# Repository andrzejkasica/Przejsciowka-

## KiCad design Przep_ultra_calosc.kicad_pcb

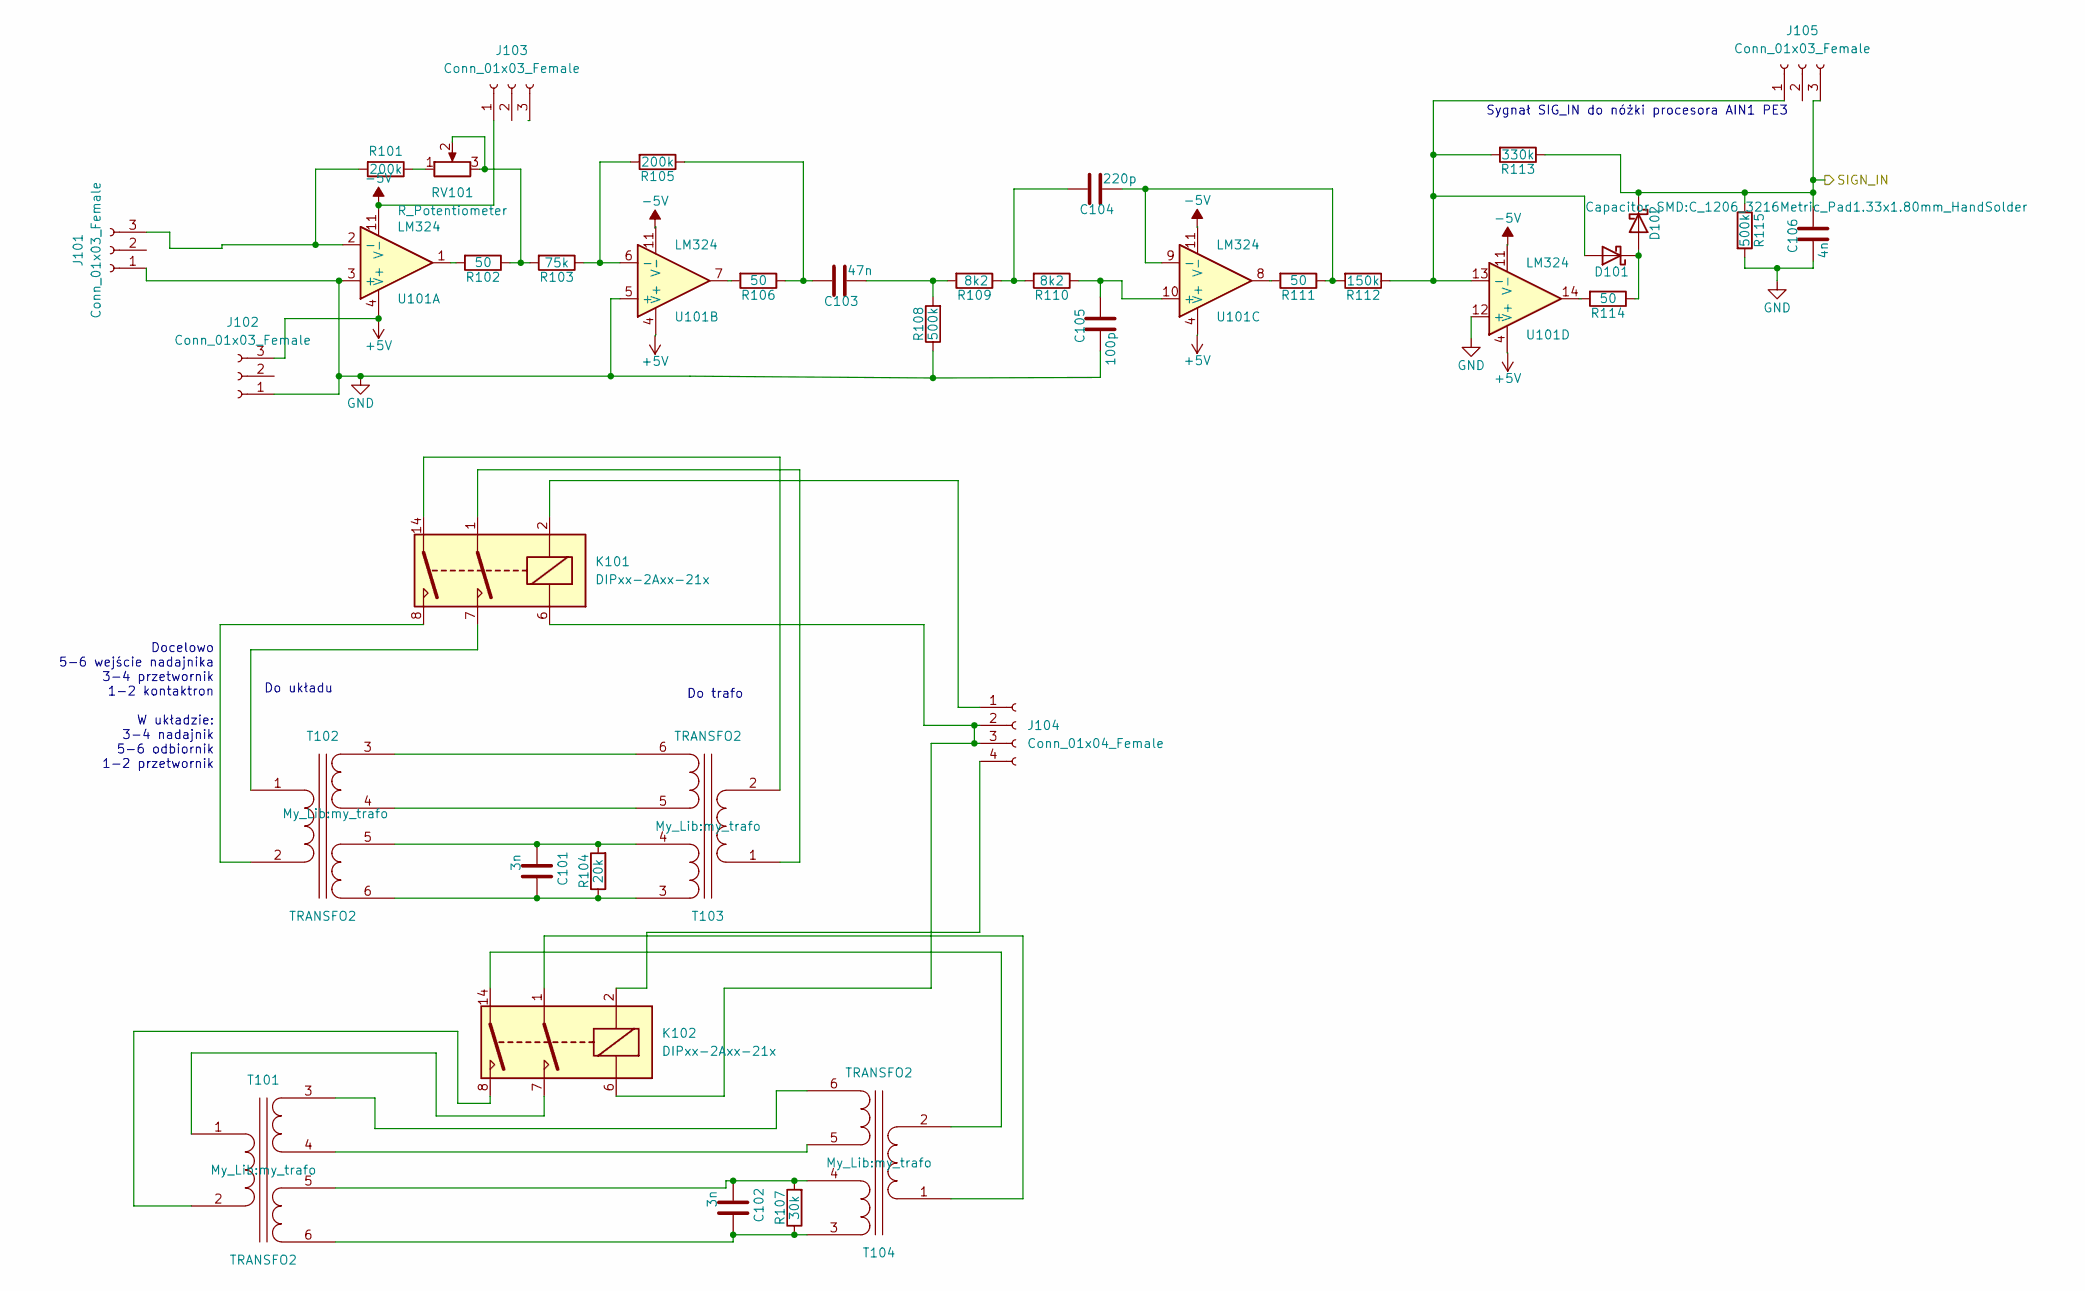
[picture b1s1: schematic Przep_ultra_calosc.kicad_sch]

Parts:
C101, C102: 3n; C_1206_3216Metric_Pad1.33x1.80mm_HandSolder
C103: 47n; C_1206_3216Metric_Pad1.33x1.80mm_HandSolder
C104: 220p; C_1206_3216Metric_Pad1.33x1.80mm_HandSolder
C105: 100p; C_1206_3216Metric_Pad1.33x1.80mm_HandSolder
C106: 4n; C_1206_3216Metric_Pad1.33x1.80mm_HandSolder
D101, D102: D_Schottky; D_MELF_Handsoldering
J101, J102, J103, J105: Conn_01x03_Female; PinHeader_1x03_P2.54mm_Vertical
J104: Conn_01x04_Female; PinHeader_1x04_P2.54mm_Vertical
K101, K102: DIPxx-2Axx-21x; Relay_StandexMeder_DIP_LowProfile
R101, R105: 200k; R_1206_3216Metric_Pad1.30x1.75mm_HandSolder
R102, R106, R111, R114: 50; R_1206_3216Metric_Pad1.30x1.75mm_HandSolder
R103: 75k; R_1206_3216Metric_Pad1.30x1.75mm_HandSolder
R104: 20k; R_1206_3216Metric_Pad1.30x1.75mm_HandSolder
R107: 30k; R_1206_3216Metric_Pad1.30x1.75mm_HandSolder
R108, R115: 500k; R_1206_3216Metric_Pad1.30x1.75mm_HandSolder
R109, R110: 8k2; R_1206_3216Metric_Pad1.30x1.75mm_HandSolder
R112: 150k; R_1206_3216Metric_Pad1.30x1.75mm_HandSolder
R113: 330k; R_1206_3216Metric_Pad1.30x1.75mm_HandSolder
RV101: R_Potentiometer; Potentiometer_Bourns_3296W_Vertical
T101, T102, T103, T104: TRANSFO2; my_trafo
U101: LM324; SOIC-14_3.9x8.7mm_P1.27mm

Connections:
+5V: J102.3, U101.4 (V+)
-5V: J103.1, U101.11 (V-)
/SIGN_IN: C106.2, D102.1 (K), J105.3, R113.1, R115.1
GND: C105.1, C106.1, J101.1, J102.1, R108.1, R115.2, U101.3 (+), U101.5 (+), U101.12 (+)
unnamed: C101.1, R104.1, T102.6 (SD), T103.3 (SA)
unnamed: C101.2, R104.2, T102.5 (SC), T103.4 (SB)
unnamed: C102.1, R107.1, T101.6 (SD), T104.3 (SA)
unnamed: C102.2, R107.2, T101.5 (SC), T104.4 (SB)
unnamed: C103.1, R108.2, R109.2
unnamed: C103.2, R105.1, R106.1
unnamed: C104.1, R111.1, R112.2, U101.9 (-)
unnamed: C104.2, R109.1, R110.2
unnamed: C105.2, R110.1, U101.10 (+)
unnamed: D101.1 (K), D102.2 (A), R114.1
unnamed: D101.2 (A), J105.1, R112.1, R113.2, U101.13 (-)
unnamed: J101.3, R101.2, U101.2 (-)
unnamed: J104.1, K101.2
unnamed: J104.2, J104.3, K101.6, K102.6
unnamed: J104.4, K102.2
unnamed: K101.1, T103.1 (AA)
unnamed: K101.7, T102.1 (AA)
unnamed: K101.8, T102.2 (AB)
unnamed: K101.14, T103.2 (AB)
unnamed: K102.1, T104.1 (AA)
unnamed: K102.7, T101.1 (AA)
unnamed: K102.8, T101.2 (AB)
unnamed: K102.14, T104.2 (AB)
unnamed: R101.1, RV101.1
unnamed: R102.1, R103.2, RV101.2, RV101.3
unnamed: R102.2, U101.1
unnamed: R103.1, R105.2, U101.6 (-)
unnamed: R106.2, U101.7
unnamed: R111.2, U101.8
unnamed: R114.2, U101.14
unnamed: T101.3 (SA), T104.6 (SD)
unnamed: T101.4 (SB), T104.5 (SC)
unnamed: T102.3 (SA), T103.6 (SD)
unnamed: T102.4 (SB), T103.5 (SC)

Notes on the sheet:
Do trafo
Docelowo 5-6 wejście nadajnika 3-4 przetwornik 1-2 kontaktron W układzie: 3-4 nadajnik 5-6 odbiornik 1-2 przetwornik
Do układu
Sygnał SIG_IN do nóżki procesora AIN1 PE3

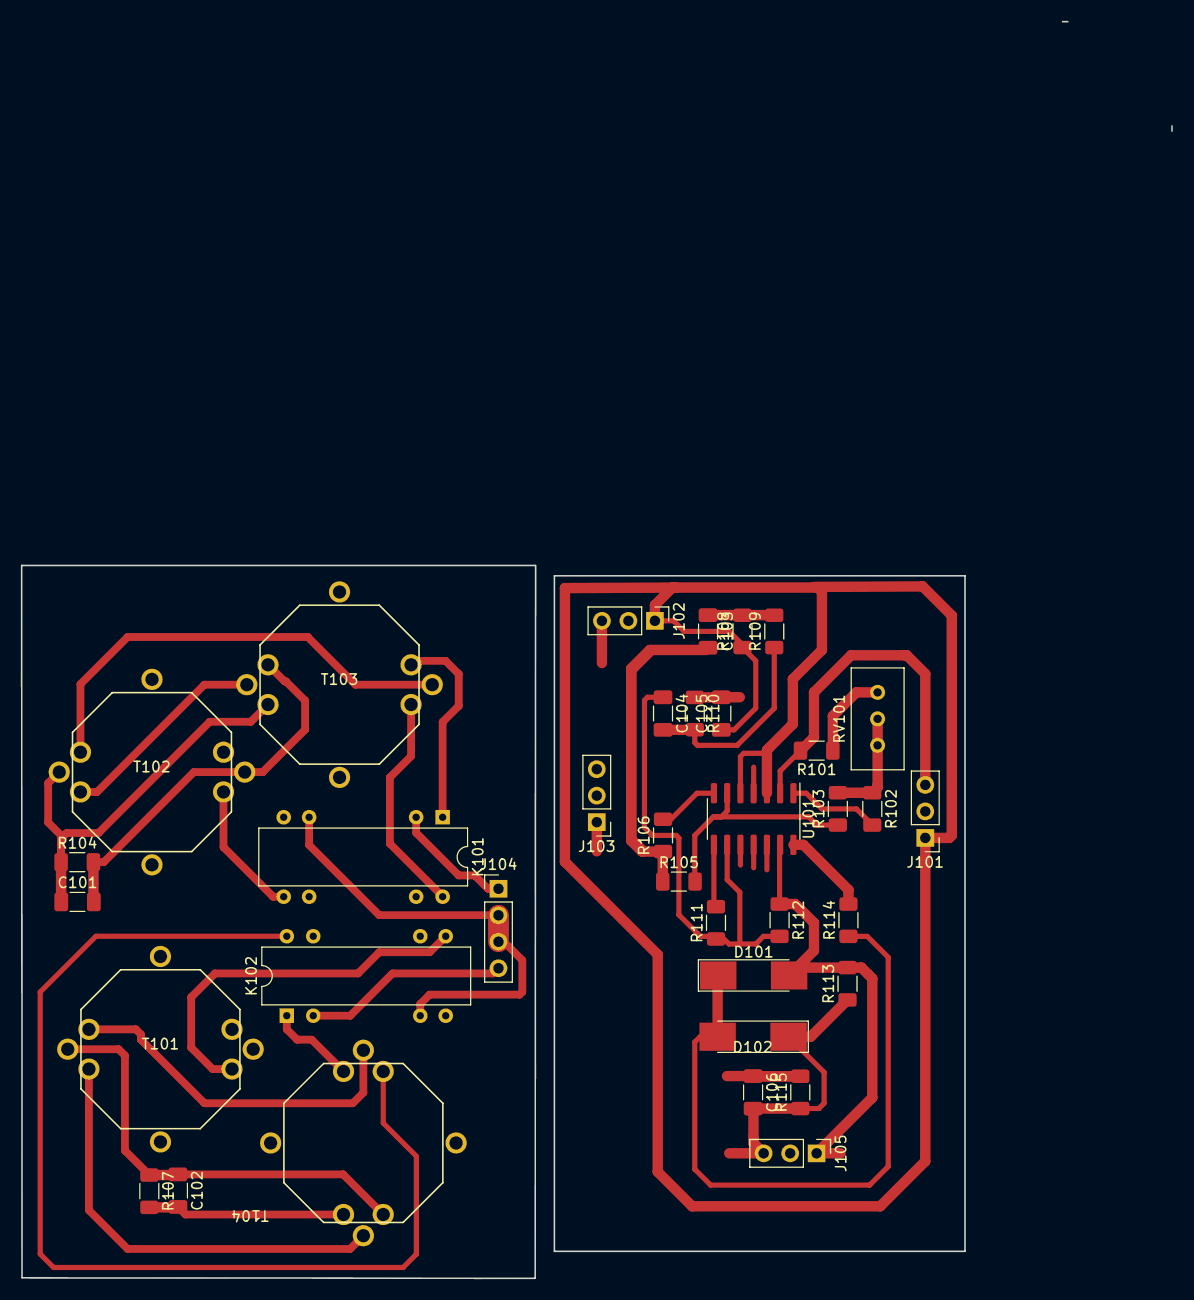
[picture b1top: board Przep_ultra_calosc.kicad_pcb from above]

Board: 2 copper layers, 110.3 x 120.5 mm, 36 parts (0 on the bottom side), 38 nets.
